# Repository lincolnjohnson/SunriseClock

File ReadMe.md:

# Arduino SunriseClock v3.2 #
https://github.com/lincolnjohnson/SunriseClock
ReadMe file  
Lincoln Johnson August 2016

---

## Introduction ##

An LED sunrise clock using an Arduino Pro Micro, 5M 5630 LED strip (300 LEDs/strip), HT1632C 8X32 LED module, DS3231 RTC Module, and rotary encoder with built-in switch.

I've tried a few of the commercially available sunrise clocks, and none of them seem to go bright enough to really help me wake up. So I went with "bigger is better," and maybe a little too far. The LED strip pulls ~72W of power at full brightness, and at 8.5% is sufficient as a standalone light to read or work by.

Should provide ~10,000 lumens at full brightness. Compare that to off-the-shelf sunrise clocks, which generally provide ~300-800 lumens... It's bright enough to hurt my eyes from across the room, and definitely gets me out of bed. I didn't build in functionality to limit the brightness or change the sunrise length, but these would be reasonably trivial to implement if desired.

The clock can be set to natually shift along with the natural sunrise if desired so that you wake up with the real sunrise during the summer months when it shifts earlier.

I've included a schematic and Eagle files for PCB printing. The PCB is designed to be split into two boards, one for the arduino, one for the rotary encoder and switch to be mounted near the top of the case I've designed. Case plans are in the Drawings folder.

Functionality included:

- 16-bit PWM control of LED lamp brightness
- Sunrise brightness uses an exponential function to ramp up brightness in a way that appears linear to the human eye
- User defined Sunrise (alarm) start time, ramps up over 30 minutes
- Choose to have sunrise follow the natural sunrise time or not (with the latest time being the above defined time)
- Automatic dimming after two hours at full brightness
- User-adjustable brightness of light when outside of sunrise period
- Set RTC clock using rotary encoder
- Automatic RTC adjustment for DST
- TODO: ADD WEEKEND AUTOMATIC ADJUSTMENT FOR EXTRA SLEEP TIME

Essentially, once initial program is loaded onto clock it never needs to be re-connected unless you want to update the baseline functionality. You can do everything you should need to do through the various menus.

I made some minor adjustments to a couple of the included libraries or used non-standard versions, so they're included in this repository as well so as to make your life easier if you want to compile/build this. Everything in the includes folder is not my own original work. The other included files listed such as EEPROM and Wire are standard arduino versions.

There are dual signal wires to the MOSFET controlling the LEDs because it seemed that one signal wire wasn't allowing the system to open fully when using a transistor. Not sure why, but doubling up appears to have fixed it - at full duty cycle it's just as bright as a direct connection to power, especially with the first MOSFET switching the source voltage to drive the second one. Now that I've switched to using a MOSFET, one is fine but two signals doesn't hurt so I left it. If you need the extra pin for something else you can always remove one of 9/10 and update the code appropriately.

The Pro Micro tends to be cranky with the Arduino IDE sometimes, especially if you are trying to load code to it for the first time, or switching between sketches. I find that jumpering the RST and GND pins, pressing upload on the IDE, and then disconnecting the jumper as soon as the IDE finishes compiling and outputs the size of the files used fixes this problem. Subsequent uploads with the same sketch should work fine. Not sure if this is a problem related to my use of cheap ebay clones.

I strongly suggest you use a high-quality power supply, as when cheap ebay ones start to die they tend to send out significant voltage spikes that fry things... such as your Arduino.

"Arduino SunriseClock v3.2" by Lincoln Johnson is licensed under CC BY-SA 4.0.
Included libraries are licensed under the licenses provided by their respective creators.

## Usage notes ##

- Run InitialSetup.ino on your Arduino board to initialize EEPROM values and set the time on your RTC [alternatively, these can all be set through the configuration menu]
- Update latitude and longitude values for your location in SunriseClock.ino
- Run SunriseClock.ino on your Arduino board

Pushbutton used to:

- Cancel sunrise if you wake up before it completes
- Toggle clock and light on or off when outside sunrise period and not in configuration menu
- Go back one level in configuration menu, or exit config if on top level

Rotary encoder used to:

- Cycle between configuration menu options or option settings
- Pushbutton used to enter config menu or select menu option displayed

## Electronics BOM ##

- 1x Arduino Pro Micro (Nano also tested and works for base functionality, changes would need to be made to schematic)
- 1x 80W+ power supply (PMT-12V100W1AA)
- 1x 5m 5630 LED strip
- 1x RTC Clock (ebay DS3231 clock module board)
- 1x 8x32 LED display board with HT1632C controller
- 1x 12v->5V DC converter (BP5293-50)
- 1x Pushbutton switch (1825910-6)
- 1x Rotary encoder with pushbutton switch (EN12-HS22AF20)
- 2x 0.1uF capacitor (K104K10X7RF5UH5)
- 2x n-channel mosfet (FQU13N06L)
- 2x 100ohm resistors
- 2x 100kohm resistors
- 2x 12 pin female headers to enable easy replacement of arduino in case of failure (PPTC121LFBN-RC)
- 3x 6 pin headers to connect 3208 matrix and switches board (1x 801-87-006-20-001101 right angle for 3208 & 2x 310-87-106-41-001101 for switches)
- 1x 5 pin header to connect RTC (310-87-105-41-001101)
- 1x 2 pin header to connect LED strip (310-87-102-41-001101)
- 1x screw terminal header for power connection to power supply (1935161)
- Various hookup/connection wires
- Breadboard if no PCB

## Materials used for physical build ##

- 1x 5" to 4" ducting reducer, spray painted matte black
- 1x 4" ducting connector
- 1x 4" ducting cap
- 1x 5" DIA 9" height acrylic canister with white tissue paper as shade
- 1x AC power entry connector (701W-X2/02 or similar)
- 1x Aluminum knob for rotary encoder (Ebay)
- 1x Pushbutton cap for switch (TAGCHR)
- 4.5 ft of 6" wide hardwood for case

## Main Board Schematic ##

This is the main board without the rotary encoder and button on it. If you want it on one board, remove the TOSWITCHES headers and connect them as required.

## Eagle Main Board PCB ##

I haven't tested this board yet as it hasn't shown up from the fab. It's probably wrong/may cause a black hole to form and destroy the planet. Use at your own risk. Board size: 1.5464 sqin.

This will need additional physical wires soldered on the LED power ciruit to handle the ~72W power drain if you use the set trace length.

## Switches Board Schematic ##

This is the board with the rotary encoder and button on it. If you want it on one board, remove the TOSWITCHES headers and connect them as required.

## Eagle Switches Board PCB ##

I haven't tested this board yet as it hasn't shown up from the fab. It's probably wrong/may cause a black hole to form and destroy the planet. Use at your own risk. Board size: 1.1135 sqin.

## Case Design ##

Complete drawings follow below. Sides not shown as they are solid. PDF with full instructions for construction in Drawings folder.

###Completed case

###Base drawings

###Front drawings

###Top drawings

###Back drawings

## SunriseClock Functions ##

###ISR(PCINT0_vect)
#####Description
Reads the inputs from the rotary encoder gray code to determine if an increment or decrement is desired

###void stop()
#####Description
Called by interrupt, reads the inputs from pushbutton with software debouncing
#####Syntax
`stop();`
#####Parameters
None.
#####Returns
Nothing.

###void toggleLamp(boolean on)
#####Description
Toggles lamp on or off
#####Syntax
`toggleLamp(0);`
#####Parameters
*(boolean)* on - 0 or false is off, 1 or true is on
#####Returns
Nothing.

###void timeUpdate()
#####Description
Called by interrupt generated by 1HZ square wave from RTC - calls showClock() if lamp is on
#####Syntax
`timeUpdate();`
#####Parameters
None.
#####Returns
Nothing.

###void ShowClock()
#####Description
Updates clock display based on current time
#####Syntax
`ShowClock();`
#####Parameters
None.
#####Returns
Nothing.

###bool IsDST()
#####Description
Checks if current time is in DST or not
#####Syntax
`IsDST();`
#####Parameters
None.
#####Returns
0 if currently not in DST, 1 if in DST

###void CheckDST()
#####Description
Checks if currently in DST, updates relevant EEPROM values if there has been a change, updates time on RTC
#####Syntax
`CheckDST();`
#####Parameters
None.
#####Returns
Nothing.

###void setBrightness(unsigned int set)
#####Description
Updates clock brightness
#####Syntax
`setBrightness(60000);`
#####Parameters
*(unsigned int)* set - 65536 is off, 0 is full brightness
#####Returns
Nothing.

###unsigned int readBright()
#####Description
Reads current brightness setting
#####Syntax
`readBright();`
#####Parameters
None.
#####Returns
Current brightness level *(unsigned int)*

###void getSunrise()
#####Description
Calculates sunrise time for next day, updates RTC alarm as necessary
#####Syntax
`getSunrise();`
#####Parameters
None.
#####Returns
Nothing.

###void toggleBlink(boolean blinky)
#####Description
Toggles 250ms blink cycle on LED screen
#####Syntax
`toggleBlink(true);`
#####Parameters
*(boolean)* blinky
#####Returns
Nothing.

###void ClockMenu(String text)
#####Description
Updates LED screen (for when in configuration menu)
#####Syntax
`ClockMenu("Set Clk");`
#####Parameters
*(String)* text
#####Returns
Nothing.

###void knobPress()
#####Description
Controls functionality of rotary encoder switch. Enters menu if currently in clock mode, otherwise selects current menu item shown on LED. Includes software debounce.
#####Syntax
`knobPress();`
#####Parameters
None.
#####Returns
Nothing.

###void KnobSelect()
#####Description
Updates LCD screen for menu navigation
#####Syntax
`KnobSelect();`
#####Parameters
None.
#####Returns
Nothing.

###void KnobUpdate()
#####Description
Called by encoder ISR. Controls update of all config variables, EEPROM updates as necessary.
#####Syntax
`KnobUpdate();`
#####Parameters
None.
#####Returns
Nothing

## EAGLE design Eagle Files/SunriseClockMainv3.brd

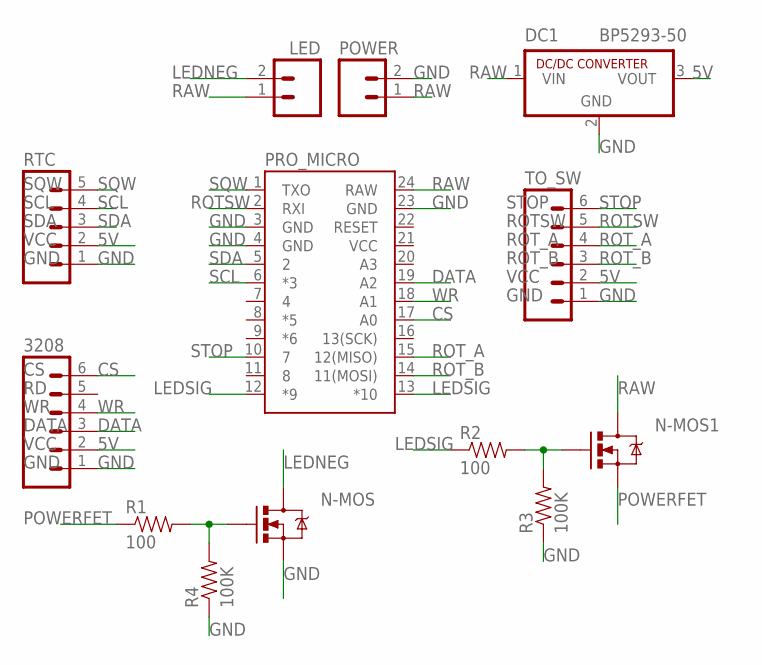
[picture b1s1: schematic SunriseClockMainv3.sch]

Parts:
3208: M06LOCK; 1X06_LOCK
DC1: BP5293-50; SIP3
LED: M02LOCK; 1X02_LOCK
N-MOS, N-MOS1: MOSFET-NCHANNELFQP30N06L; TO220V
POWER: M025MM; SCREWTERMINAL-5MM-2
PRO_MICRO: ARDUINO_PRO_MICRO
R1, R2: 100; AXIAL-0.4
R3, R4: 100K; AXIAL-0.4
RTC: M05LOCK; 1X05_LOCK
TO_SW: M06LOCK; 1X06_LOCK

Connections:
5V: 3208.2, DC1.3 (VOUT), RTC.2, TO_SW.2
CS: 3208.6, PRO_MICRO.17 (A0)
DATA: 3208.3, PRO_MICRO.19 (A2)
GND: 3208.1, DC1.2 (GND), N-MOS.3 (S), POWER.2, PRO_MICRO.3 (GND), PRO_MICRO.4 (GND), PRO_MICRO.23 (GND), R3.P$1 (1), R4.P$1 (1), RTC.1, TO_SW.1
LEDNEG: LED.2, N-MOS.2 (D)
LEDSIG: PRO_MICRO.12 (*9), PRO_MICRO.13 (*10), R2.P$1 (1)
unnamed: N-MOS.1 (G), R1.P$2 (2), R4.P$2 (2)
unnamed: N-MOS1.1 (G), R2.P$2 (2), R3.P$2 (2)
POWERFET: N-MOS1.3 (S), R1.P$1 (1)
RAW: DC1.1 (VIN), LED.1, N-MOS1.2 (D), POWER.1, PRO_MICRO.24 (RAW)
ROTSW: PRO_MICRO.2 (RXI), TO_SW.5
ROT_A: PRO_MICRO.15 (12(MISO)), TO_SW.4
ROT_B: PRO_MICRO.14 (11(MOSI)), TO_SW.3
SCL: PRO_MICRO.6 (*3), RTC.4
SDA: PRO_MICRO.5 (2), RTC.3
SQW: PRO_MICRO.1 (TXO), RTC.5
STOP: PRO_MICRO.10 (7), TO_SW.6
WR: 3208.4, PRO_MICRO.18 (A1)

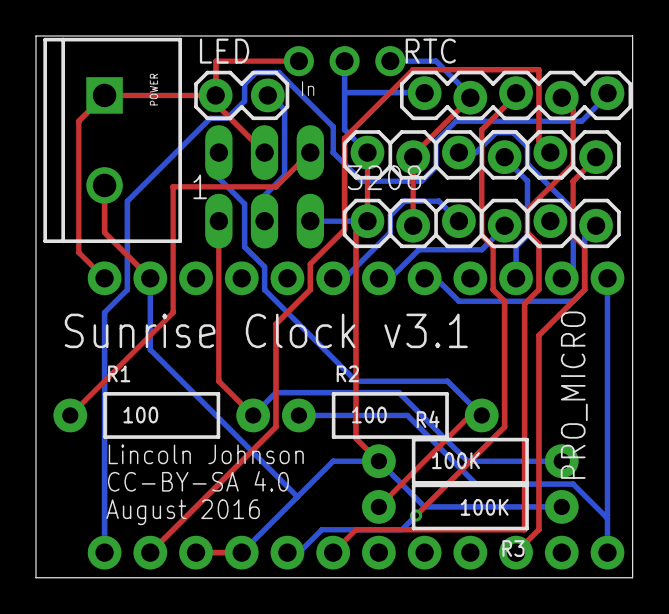
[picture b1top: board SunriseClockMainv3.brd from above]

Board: 2 copper layers, 33.1 x 30.1 mm, 13 parts (0 on the bottom side), 18 nets.

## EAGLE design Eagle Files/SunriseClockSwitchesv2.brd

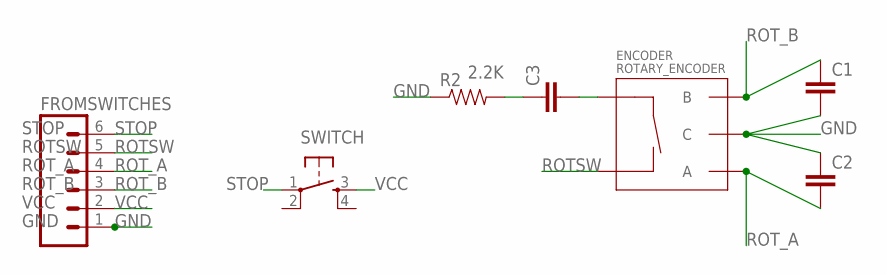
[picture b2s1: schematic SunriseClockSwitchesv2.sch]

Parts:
C1, C2, C3: CAPEZ; CAP-PTH-SMALLEZ
ENCODER: ROTARY_ENCODER; ROTARY_ENC_PLAIN
FROMSWITCHES: M06LOCK; 1X06_LOCK
R2: RESISTORPTH-1/4W; AXIAL-0.4
SWITCH: TAC_SWITCHPTH; TACTILE-PTH

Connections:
GND: C1.2, C2.1, ENCODER.C, FROMSWITCHES.1, R2.P$1 (1)
unnamed: C3.1, R2.P$2 (2)
unnamed: C3.2, ENCODER.SW+
ROTSW: ENCODER.SW-, FROMSWITCHES.5
ROT_A: C2.2, ENCODER.A, FROMSWITCHES.4
ROT_B: C1.1, ENCODER.B, FROMSWITCHES.3
STOP: FROMSWITCHES.6, SWITCH.1
VCC: FROMSWITCHES.2, SWITCH.3

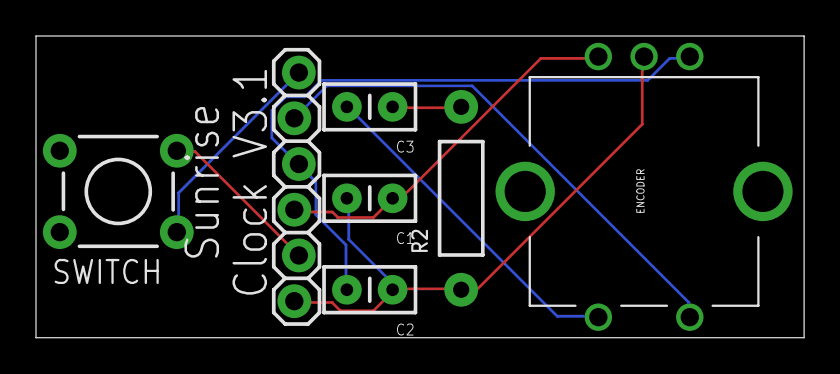
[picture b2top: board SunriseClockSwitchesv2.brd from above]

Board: 2 copper layers, 42.7 x 16.8 mm, 7 parts (0 on the bottom side), 8 nets.

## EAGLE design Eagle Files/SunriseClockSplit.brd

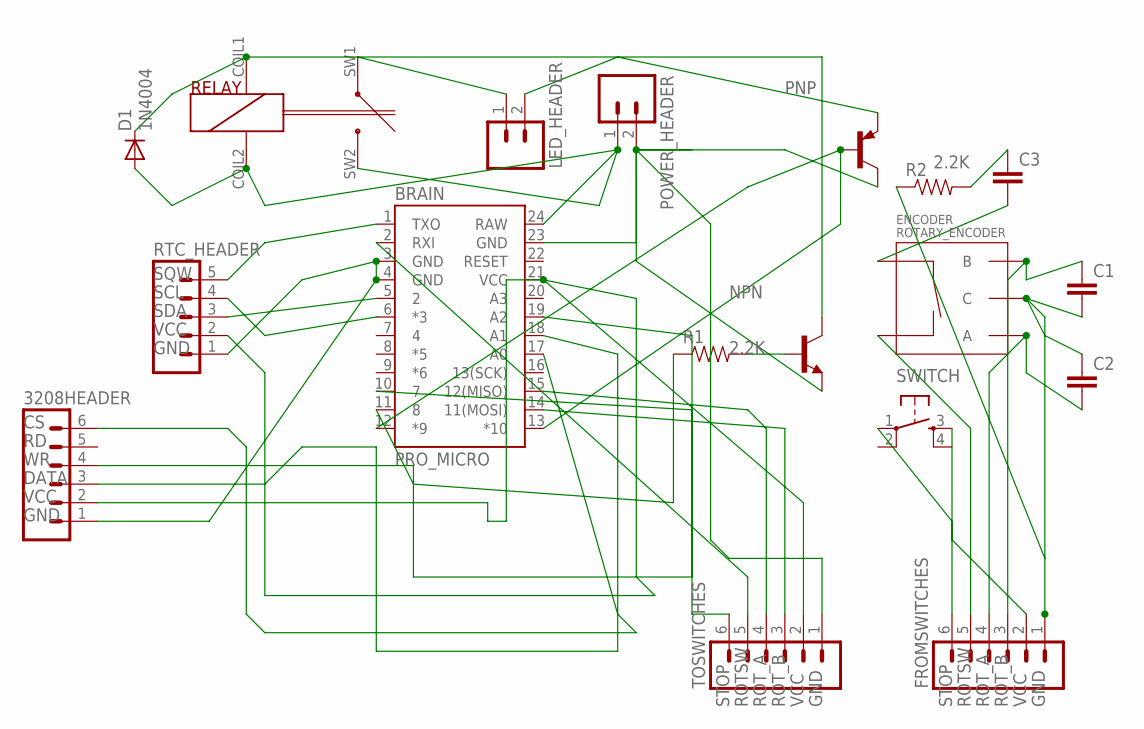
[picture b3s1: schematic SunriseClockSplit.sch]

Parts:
3208HEADER: M06LOCK; 1X06_LOCK
BRAIN: PRO_MICRO; ARDUINO_PRO_MICRO
C1, C2, C3: CAPEZ; CAP-PTH-SMALLEZ
D1: 1N4004; DO41-10
ENCODER: ROTARY_ENCODER; ROTARY_ENC_PLAIN
FROMSWITCHES: M06LOCK; 1X06_LOCK
LED_HEADER: M02LOCK; 1X02_LOCK
NPN: -NPN-TO126V; TO126V
PNP: -PNP-TO126V; TO126V
POWER_HEADER: M025MM; SCREWTERMINAL-5MM-2
R1, R2: RESISTORPTH-1/4W; AXIAL-0.4
RELAY: RELAY; HALLER_RELAIS_2PIN
RTC_HEADER: M05LOCK; 1X05_LOCK
SWITCH: TAC_SWITCHPTH; TACTILE-PTH
TOSWITCHES: M06LOCK; 1X06_LOCK

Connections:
unnamed: BRAIN.24 (RAW), D1.A, POWER_HEADER.1, RELAY.COIL2, RELAY.SW2
unnamed: LED_HEADER.1, RELAY.SW1
unnamed: LED_HEADER.2, PNP.1 (E)
unnamed: FROMSWITCHES.6, SWITCH.1
unnamed: BRAIN.12 (*9), BRAIN.13 (*10), PNP.3 (B)
unnamed: BRAIN.11 (8), R1.P$1 (1)
unnamed: NPN.3 (B), R1.P$2 (2)
unnamed: C1.1, ENCODER.B, FROMSWITCHES.3
unnamed: BRAIN.23 (GND), NPN.1 (E), PNP.2 (C), POWER_HEADER.2, TOSWITCHES.1
unnamed: C2.2, ENCODER.A, FROMSWITCHES.4
unnamed: C3.1, R2.P$2 (2)
unnamed: C3.2, ENCODER.SW+
unnamed: BRAIN.2 (RXI), TOSWITCHES.5
unnamed: BRAIN.10 (7), TOSWITCHES.6
unnamed: FROMSWITCHES.2, SWITCH.3
unnamed: BRAIN.1 (TXO), RTC_HEADER.5
unnamed: C1.2, C2.1, ENCODER.C, FROMSWITCHES.1, R2.P$1 (1)
unnamed: 3208HEADER.2, BRAIN.21 (VCC), RTC_HEADER.2, TOSWITCHES.2
unnamed: BRAIN.6 (*3), RTC_HEADER.4
unnamed: BRAIN.5 (2), RTC_HEADER.3
unnamed: ENCODER.SW-, FROMSWITCHES.5
unnamed: 3208HEADER.1, BRAIN.3 (GND), BRAIN.4 (GND), RTC_HEADER.1
unnamed: 3208HEADER.6, BRAIN.17 (A0)
unnamed: 3208HEADER.4, BRAIN.18 (A1)
unnamed: 3208HEADER.3, BRAIN.19 (A2)
unnamed: BRAIN.15 (12(MISO)), TOSWITCHES.4
unnamed: BRAIN.14 (11(MOSI)), TOSWITCHES.3
unnamed: D1.C, NPN.2 (C), RELAY.COIL1

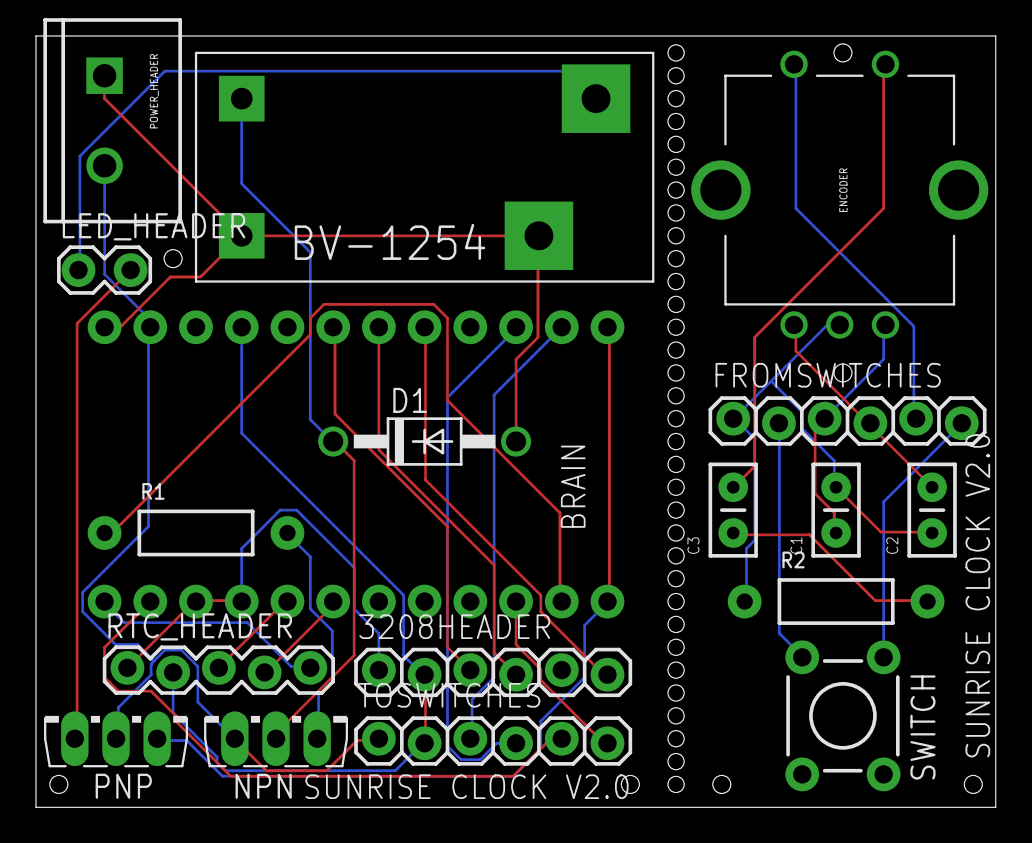
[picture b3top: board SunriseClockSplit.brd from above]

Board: 2 copper layers, 53.3 x 42.9 mm, 18 parts (0 on the bottom side), 28 nets.

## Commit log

2016-08-15 :neckbeard: Added .gitattributes & .gitignore files
2016-08-15 Code and Includes
2016-08-15 License
2016-08-16 Adding eagle files etc
2016-08-16 Adding fritzing file
2016-08-16 Read me Update
2016-08-16 I cant markdown
2016-08-16 Readme
2016-08-16 moar
2016-08-16 Fix screen not clearing when using menu with lamp off
2016-08-17 Changes, eagle is borked
2016-08-17 Revert "Changes, eagle is borked"
    This reverts commit ce4402d5bc8679ed222257ac0a5ccbb3afe4734b.
2016-08-22 Changes
    - swap MOSFET for PNP
    - constrain alarm minute to 5 minute intervals
2016-08-22 Updated Schematics
2016-08-23 version 3.0a
2016-08-23 V3.1
2016-08-23 typos
2016-08-23 Updated schematic
2016-08-24 Bigfix
2016-08-27 Adding drawings
2016-08-27 Readme updates, adding pricing doc
2016-08-27 Updated drawings
2016-10-02 Updated schematic + code
    Added DC-DC converter to limit power draw from arduino, modified
    switching circuit to have first FET driven by arduino switch the second
    FET with 12V to ensure full turn on and current drain. 5V just wasn't
    quite cutting it with these. Added auto-increase of brightness as well.
2016-10-02 Updated eagle files and schematic

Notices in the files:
parts and their libraries:
SparkFun-Connectors: Licensing: Creative Commons ShareAlike 4.0 International - https://creativecommons.org/licenses/by-sa/4.0
